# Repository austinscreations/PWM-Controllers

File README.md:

# PWM-Controllers

This project has been expanded - tehre are now controlelrs that use a sheild attached to a LilyGO POE, A board using a D1 mini. both of those baords offer 5ch of LED control

Then theres the PWM controller with 16ch expanble i2c module and the room8266 controlelr for controlling said board.

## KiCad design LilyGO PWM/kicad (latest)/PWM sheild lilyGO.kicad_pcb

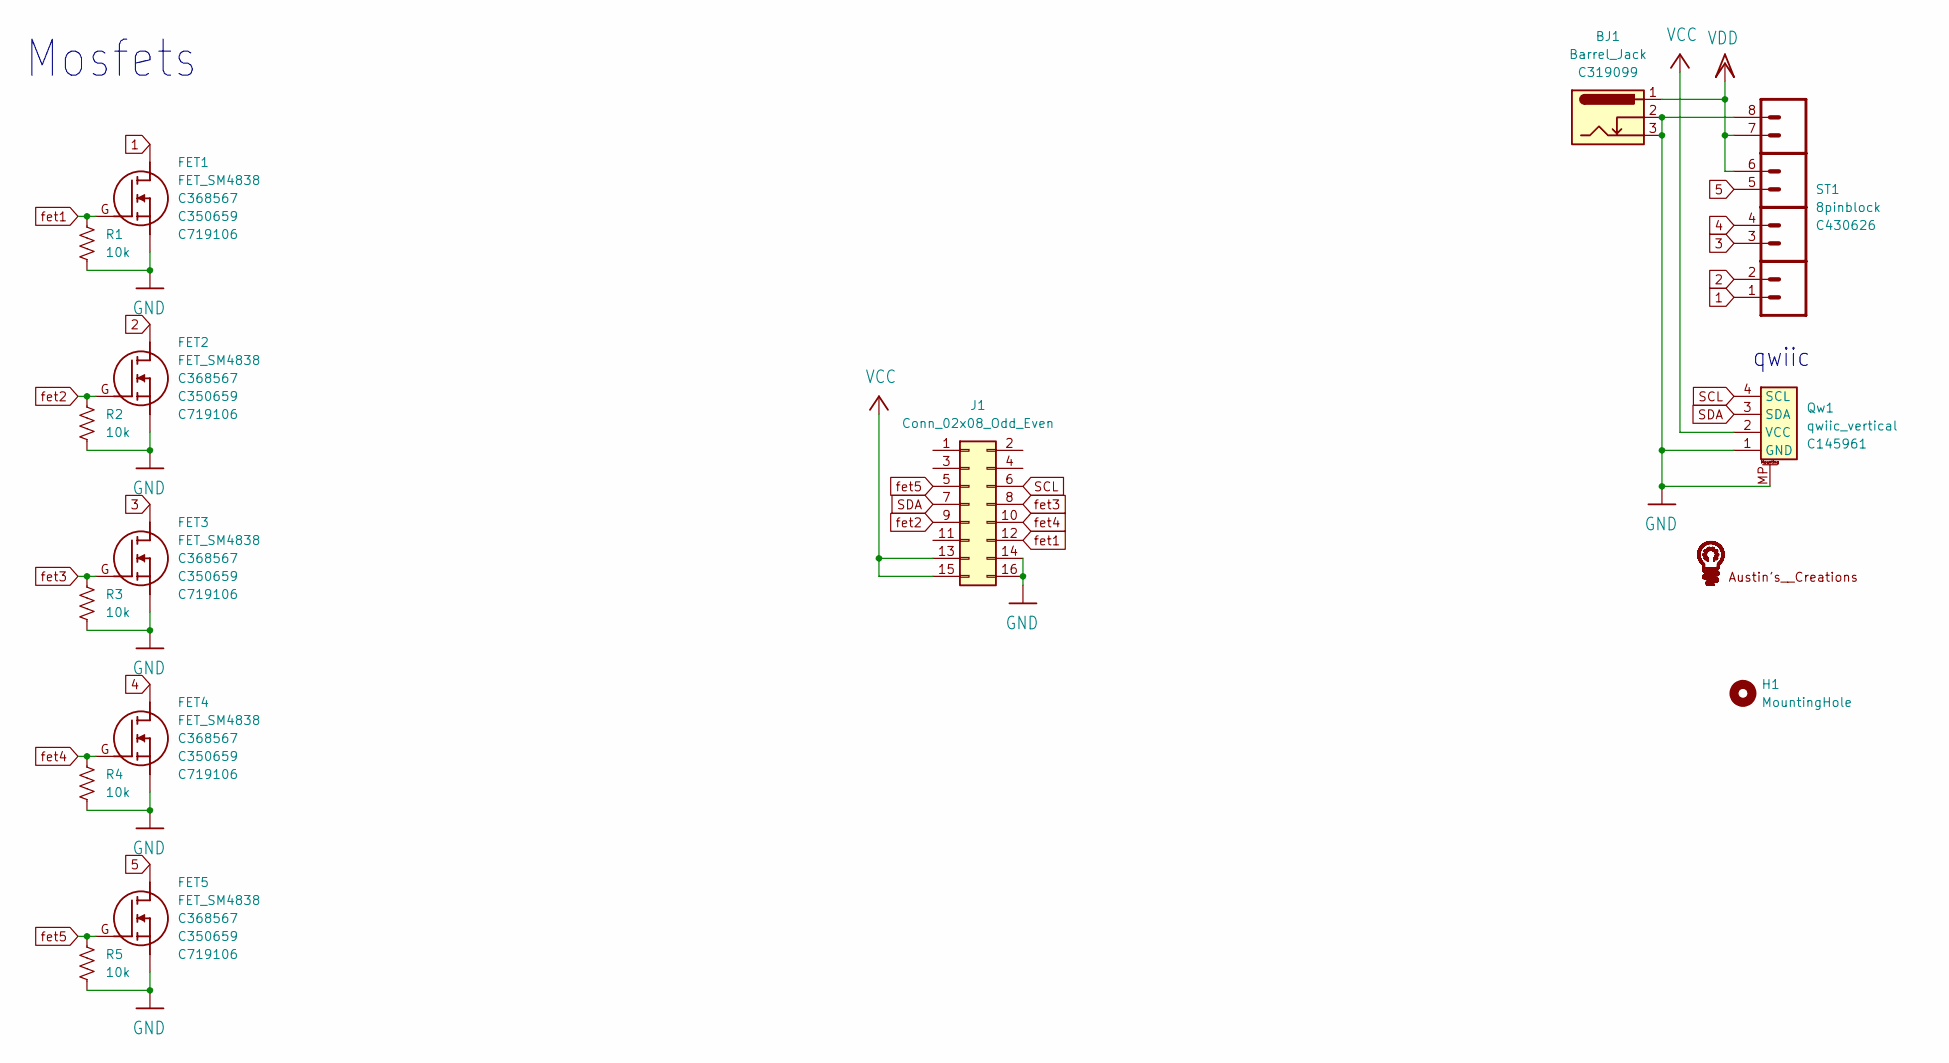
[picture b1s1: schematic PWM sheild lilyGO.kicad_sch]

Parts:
BJ1: Barrel_Jack; Barrel Jack; part # C319099
FET1, FET2, FET3, FET4, FET5: FET_SM4838; FET SM4838; part # C368567
H1: MountingHole; MountingHole_3.2mm_M3
J1: Conn_02x08_Odd_Even; PinSocket_2x08_P2.54mm_Vertical
Qw1: qwiic_vertical; qwiic vertical; part # C145961
R1, R2, R3, R4, R5: 10k; R_0603_1608Metric
ST1: 8pinblock; part # C430626
U$2: LOGO

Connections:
1: FET1.D, ST1.1
2: FET2.D, ST1.2
3: FET3.D, ST1.3
4: FET4.D, ST1.4
5: FET5.D, ST1.5
GND: BJ1.2, BJ1.3, FET1.S, FET2.S, FET3.S, FET4.S, FET5.S, J1.14, J1.16, Qw1.1 (GND), Qw1.MP, R1.2, R2.2, R3.2, R4.2, R5.2, ST1.8
SCL: J1.6, Qw1.4 (SCL)
SDA: J1.7, Qw1.3 (SDA)
VCC: J1.13, J1.15, Qw1.2 (VCC)
VDD: BJ1.1, ST1.6, ST1.7
fet1: FET1.G, J1.12, R1.1
fet2: FET2.G, J1.9, R2.1
fet3: FET3.G, J1.8, R3.1
fet4: FET4.G, J1.10, R4.1
fet5: FET5.G, J1.5, R5.1

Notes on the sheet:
qwiic
Mosfets

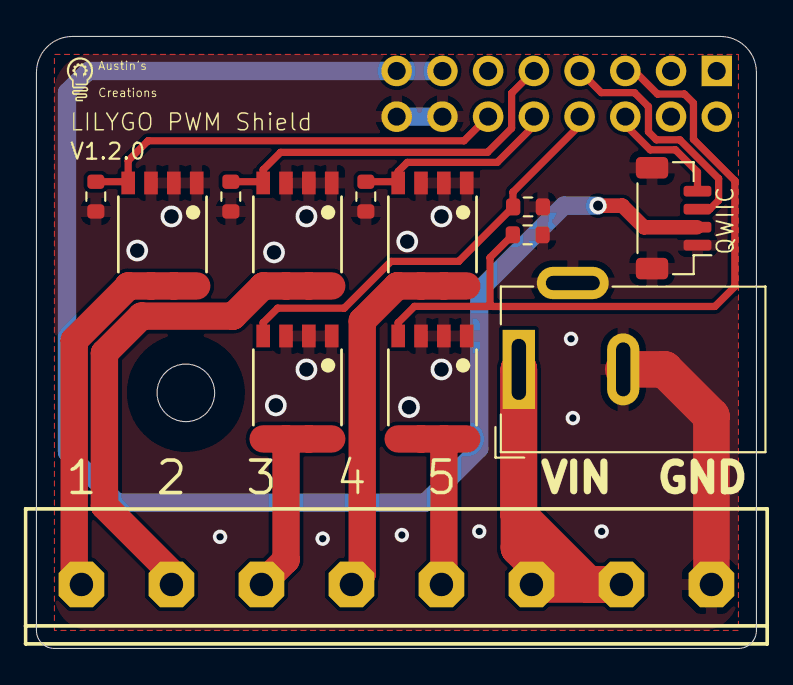
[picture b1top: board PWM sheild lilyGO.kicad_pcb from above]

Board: 2 copper layers, 40.0 x 34.0 mm, 16 parts (1 on the bottom side), 15 nets.

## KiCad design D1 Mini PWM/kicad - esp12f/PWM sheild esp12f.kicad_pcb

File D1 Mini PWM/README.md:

Placeholder

newest version is done in kicad - switched from using the D1 mini to using the esp-12f directly along with adding usb c programming and debugging support

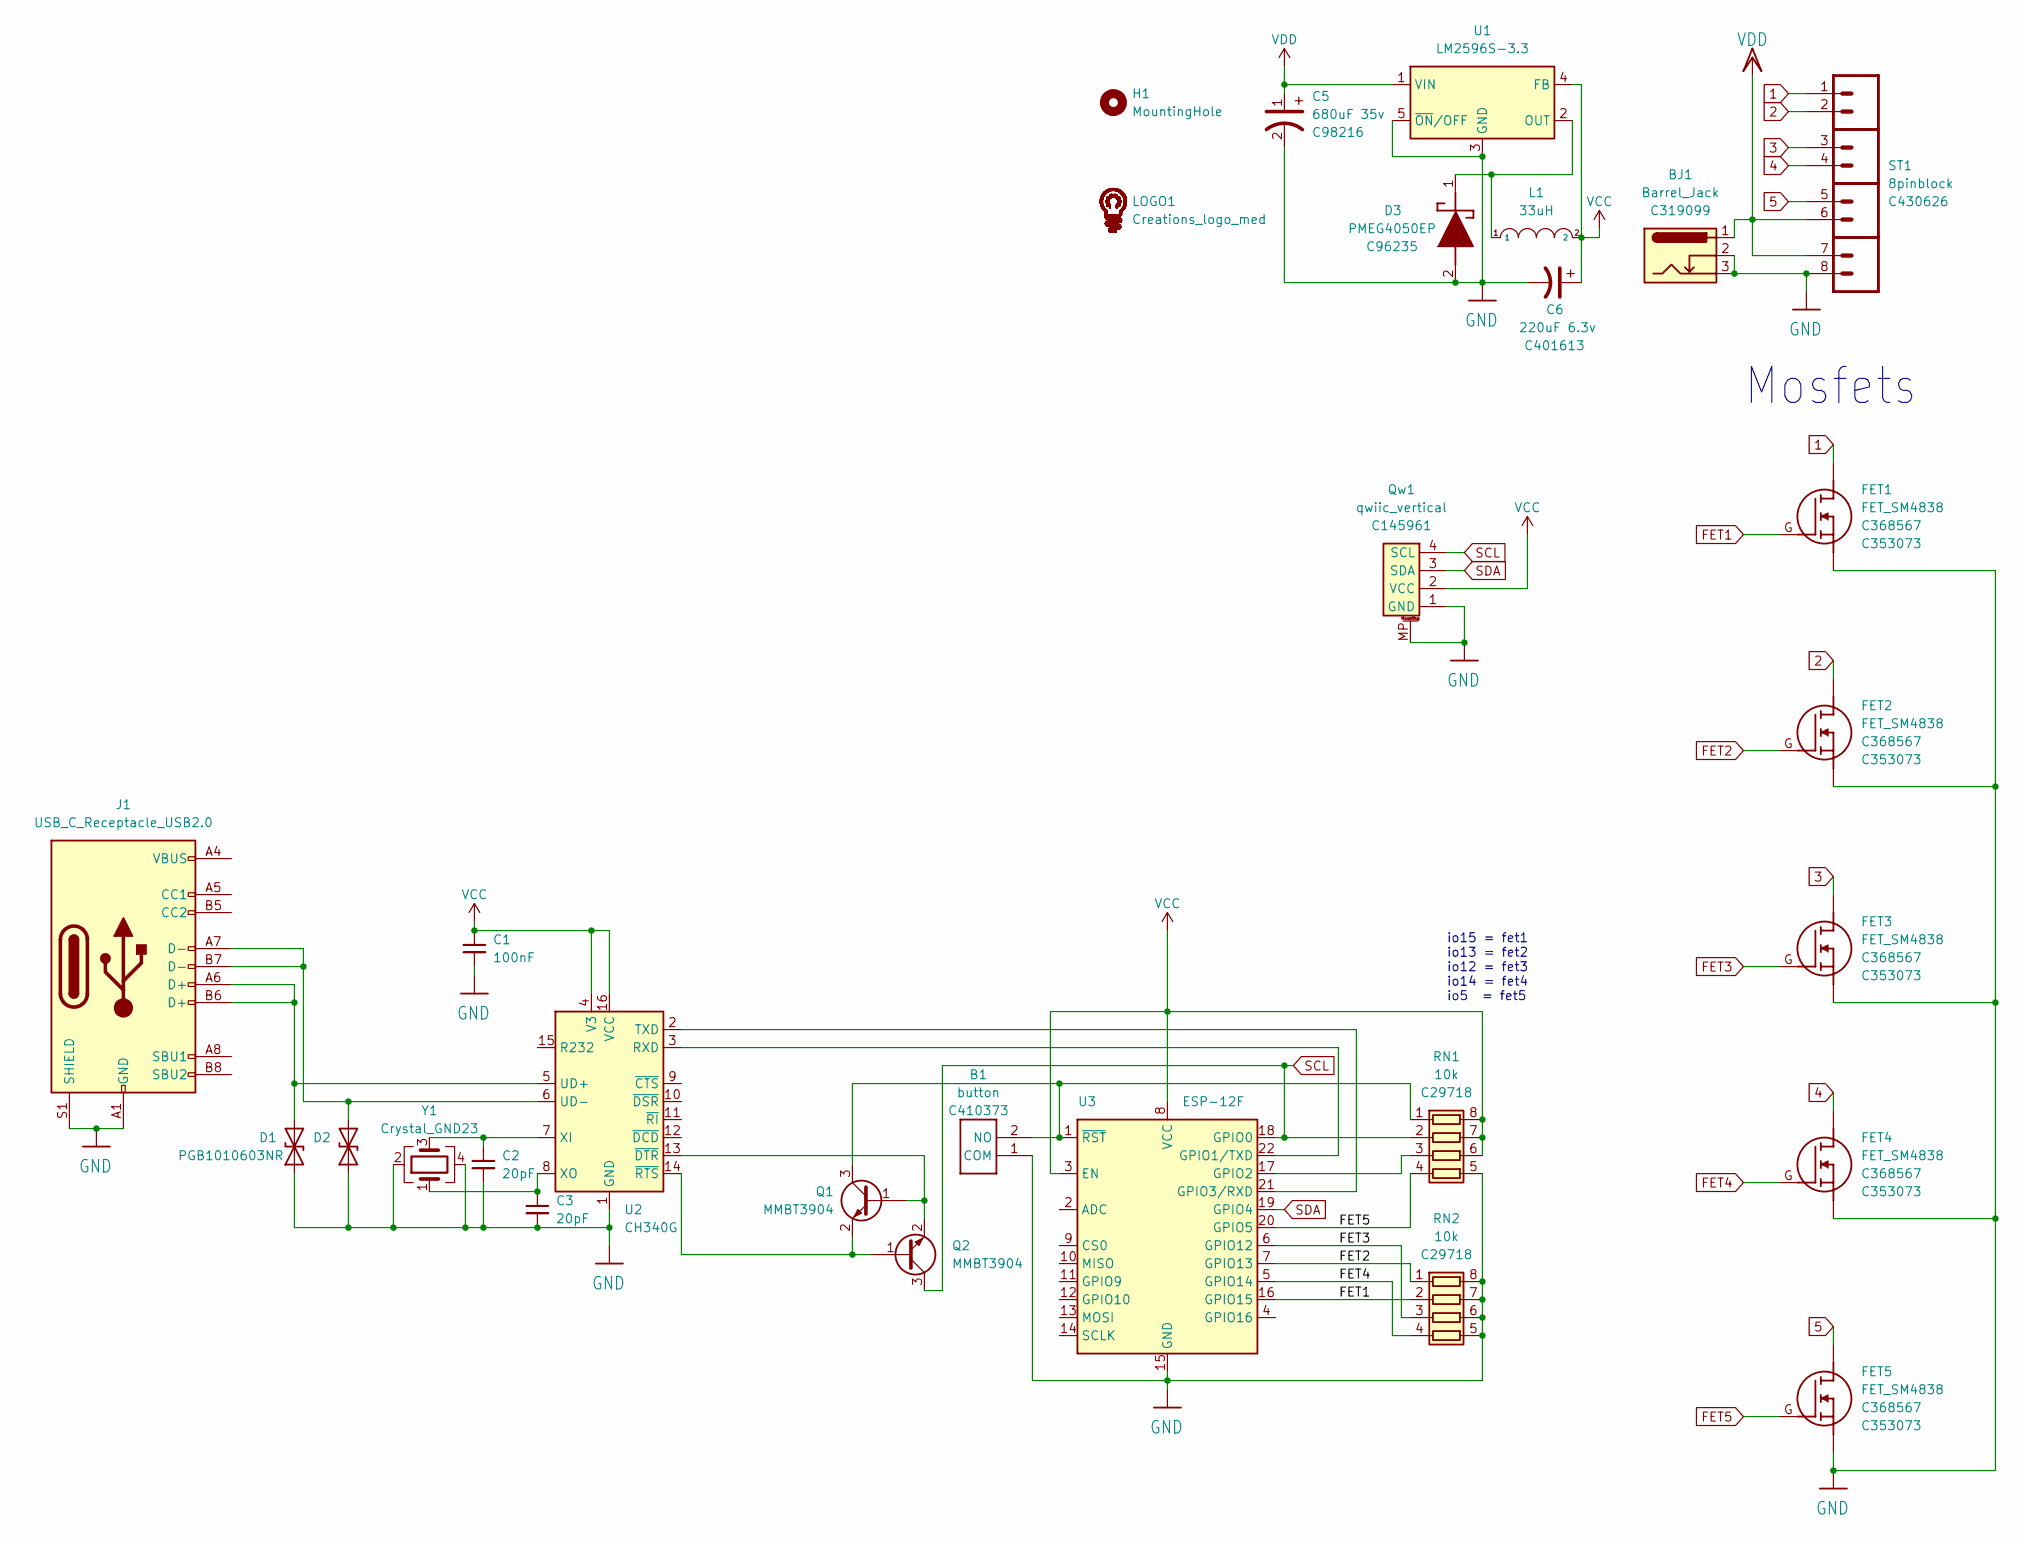
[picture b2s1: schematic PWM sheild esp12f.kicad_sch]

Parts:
B1: button; part # C410373
BJ1: Barrel_Jack; Barrel Jack; part # C319099
C1: 100nF; C_0603_1608Metric
C2, C3: 20pF; C_0603_1608Metric
C5: 680uF 35v; large capacitor 12.5d 13.5h; part # C98216
C6: 220uF 6.3v; CP_Elec_8x6.2; part # C401613
D1, D2: PGB1010603NR; D_0603_1608Metric
D3: PMEG4050EP; PMEG3050EP; part # C96235
FET1, FET2, FET3, FET4, FET5: FET_SM4838; FET SM4838; part # C368567
H1: MountingHole; MountingHole_3.2mm_M3
J1: USB_C_Receptacle_USB2.0; USB_C_Receptacle_HRO_TYPE-C-31-M-12
L1: 33uH; 12x12x8 inductor
LOGO1: Creations_logo_med; Creations logo med
Q1, Q2: MMBT3904; SOT-23
Qw1: qwiic_vertical; qwiic vertical; part # C145961
RN1, RN2: 10k; R_Array_Convex_4x0603; part # C29718
ST1: 8pinblock; part # C430626
U1: LM2596S-3.3; TO-263-5_TabPin3
U2: CH340G; SOIC-16_3.9x9.9mm_P1.27mm
U3: ESP-12F; ESP-12E
Y1: Crystal_GND23; Crystal_SMD_3225-4Pin_3.2x2.5mm

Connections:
1: FET1.D, ST1.1
2: FET2.D, ST1.2
3: FET3.D, ST1.3
4: FET4.D, ST1.4
5: FET5.D, ST1.5
FET1: FET1.G, RN2.2 (R2.1), U3.16 (GPIO15)
FET2: FET2.G, RN2.1 (R1.1), U3.7 (GPIO13)
FET3: FET3.G, RN2.3 (R3.1), U3.6 (GPIO12)
FET4: FET4.G, RN2.4 (R4.1), U3.5 (GPIO14)
FET5: FET5.G, RN1.4 (R4.1), U3.20 (GPIO5)
GND: B1.1 (COM), BJ1.2, BJ1.3, C1.2, C2.2, C3.2, C5.2, C6.2, D1.1 (A1), D2.1 (A1), D3.2 (A), FET1.S, FET2.S, FET3.S, FET4.S, FET5.S, J1.A1 (GND), J1.A12 (GND), J1.B1 (GND), J1.B12 (GND), J1.S1 (SHIELD), Qw1.1 (GND), Qw1.MP, RN1.5 (R4.2), RN2.5 (R4.2), RN2.6 (R3.2), RN2.7 (R2.2), RN2.8 (R1.2), ST1.8, U1.3 (GND), U1.5 (~ON/OFF), U2.1 (GND), U3.15 (GND), Y1.2, Y1.4
unnamed: B1.2 (NO), Q1.3 (C), RN1.1 (R1.1), U3.1 (~RST)
unnamed: C2.1, U2.7 (XI), Y1.3
unnamed: C3.1, U2.8 (XO), Y1.1
unnamed: D3.1 (K), L1.1, U1.2 (OUT)
unnamed: J1.A4 (VBUS), J1.A9 (VBUS), J1.B4 (VBUS), J1.B9 (VBUS)
unnamed: D1.2 (A2), J1.A6 (D+), J1.B6 (D+), U2.5 (UD+)
unnamed: D2.2 (A2), J1.A7 (D-), J1.B7 (D-), U2.6 (UD-)
unnamed: Q1.1 (B), Q2.2 (E), U2.13 (~DTR)
unnamed: Q1.2 (E), Q2.1 (B), U2.14 (~RTS)
unnamed: RN1.3 (R3.1), U3.17 (GPIO2)
unnamed: U2.2 (TXD), U3.21 (GPIO3/RXD)
unnamed: U2.3 (RXD), U3.22 (GPIO1/TXD)
SCL: Q2.3 (C), Qw1.4 (SCL), RN1.2 (R2.1), U3.18 (GPIO0)
SDA: Qw1.3 (SDA), U3.19 (GPIO4)
VCC: C1.1, C6.1, L1.2, Qw1.2 (VCC), RN1.6 (R3.2), RN1.7 (R2.2), RN1.8 (R1.2), U1.4 (FB), U2.4 (V3), U2.16 (VCC), U3.3 (EN), U3.8 (VCC)
VDD: BJ1.1, C5.1, ST1.6, ST1.7, U1.1 (VIN)

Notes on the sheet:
io15 = fet1 io13 = fet2 io12 = fet3 io14 = fet4 io5 = fet5
Mosfets

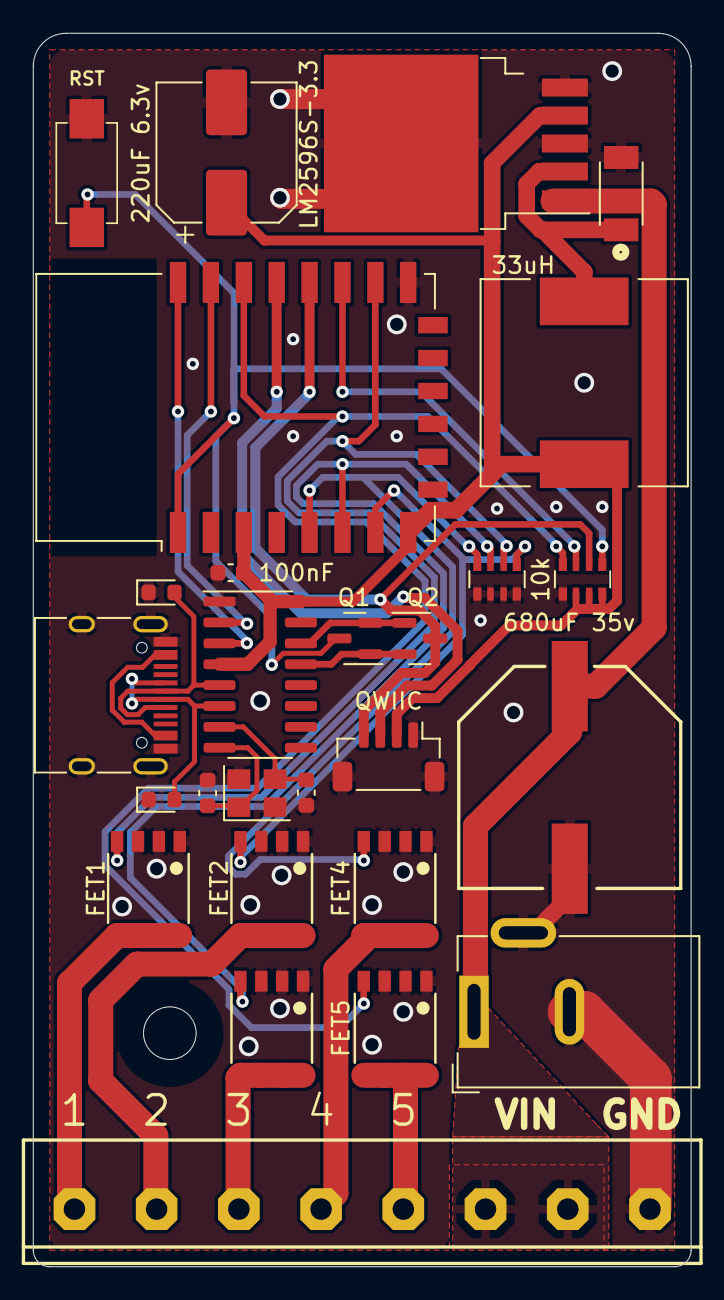
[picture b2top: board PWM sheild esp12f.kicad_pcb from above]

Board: 2 copper layers, 40.0 x 75.0 mm, 29 parts (1 on the bottom side), 27 nets.

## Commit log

2021-08-06 Create LICENSE
2021-08-06 Add files via upload
    added missing vertical measurements for holes
2021-08-13 Add files via upload
    adding code
2021-08-13 Update README.md
    add video demo link
2021-09-16 updating example flow
    updated the example flow to use less mqtt nodes to make setup easier.
2021-10-14 Add files via upload
    adding 3d printable cases
    this holds both the PWM controller and the room8266 controller
2022-01-25 project scope increase
2022-01-25 Rename readme.md to README.md
2022-01-25 Create 3D Printable Cases
2022-01-26 updating stub tolerance for mating with lid
2022-12-27 no longer relevant
